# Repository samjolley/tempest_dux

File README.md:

# Tempest Dux

A wireless split ergonomic keyboard with an integrated trackball. Thirty-six keys, low-profile Choc switches, nice!nano v2, nice!view display, and a PMW3610 trackball on the right half.

This is my build. I did not design it from scratch, and the credits below matter.

## Lineage and credits

- **Ergonomics:** the dux family, Rae-Dux and Architeuthis Dux.
- **Base design and visual theme:** [thrly's Tempest](https://github.com/thrly/tempest).
- **Firmware base:** [Manna Harbour's Miryoku](https://github.com/manna-harbour/miryoku) for ZMK.
- **Trackball driver:** [badjeff's PMW3610 module](https://github.com/badjeff/zmk-pmw3610-driver).

## What is mine

Built on that lineage, my own contribution is:

- a custom PCB laid out with Ergogen and finished in KiCad (matrix, MCU, display, power, and the trackball cluster),
- the integrated PMW3610 trackball on the right half, its socket, and the printed housing,
- custom outlines and multi-layer 3D-printed plates and case,
- the ZMK firmware integration that makes the trackball a first-class input alongside the keys.

## Status

- **v0.6.56** boards fabricated and in assembly and bring-up.
- **v0.7.x** in progress: the reversible board architecture is dropped in favor of separate left and right files, with mounting-hole clearance, test points, and a dual-face ground pour on the errata list.

## Build log

I wrote up the design decisions, the failures, and what I would do differently here: <https://samjolley.com/writing/building-the-tempest-dux/>

## License

My original work here (the Ergogen config, the KiCad board, and my custom footprints) is released under the MIT License; see [LICENSE](LICENSE). Bundled third-party components keep their own licenses: the `ceoloide` Ergogen footprints under `ergogen/footprints/ceoloide/` retain the license headers in each file. This design builds on the prior art credited above, which carries its own terms where stated.

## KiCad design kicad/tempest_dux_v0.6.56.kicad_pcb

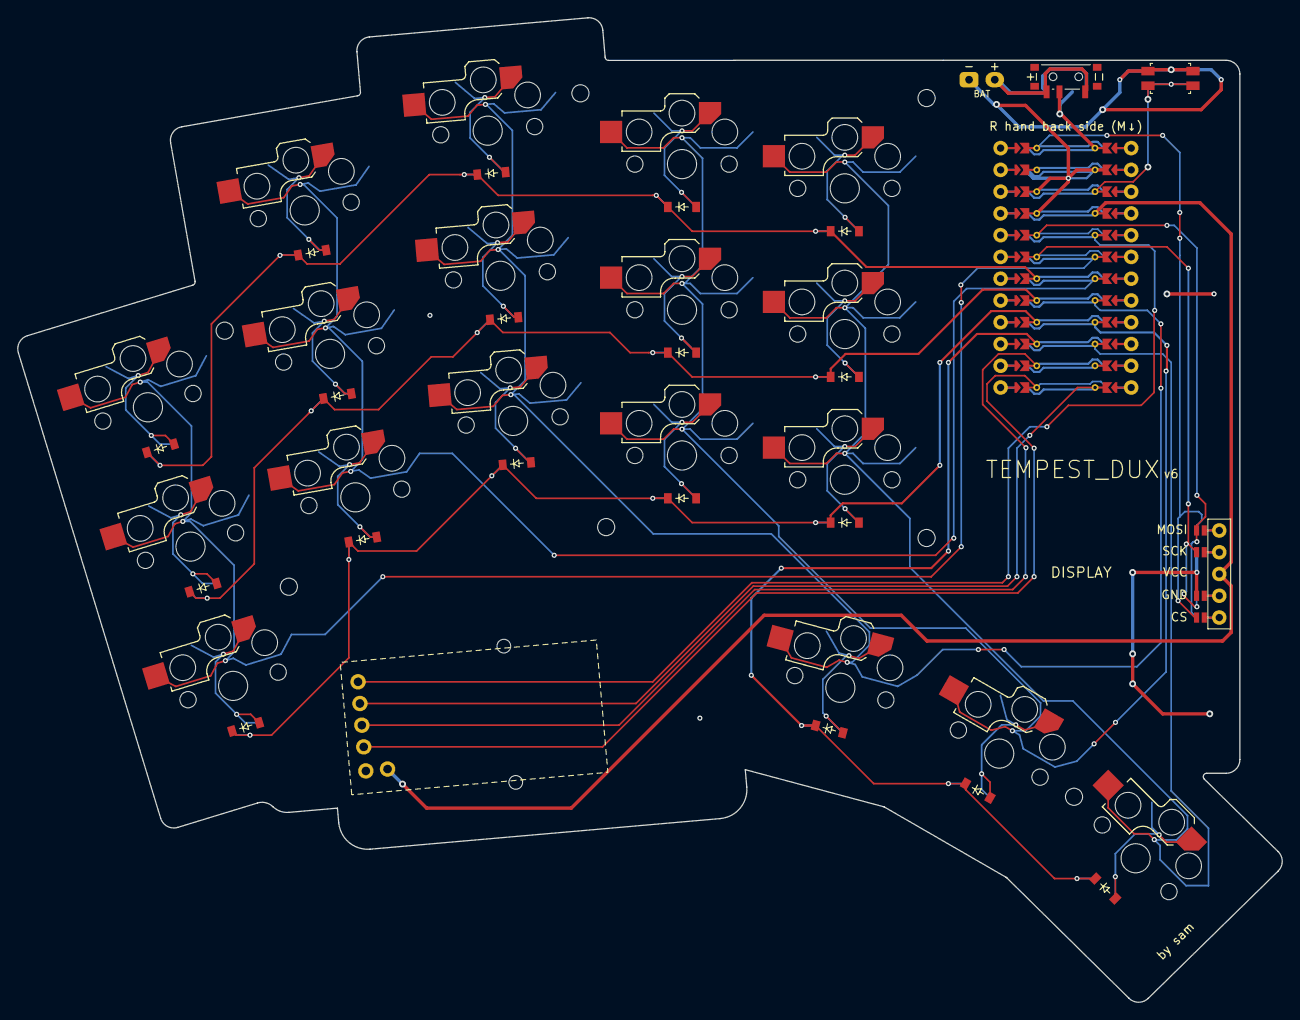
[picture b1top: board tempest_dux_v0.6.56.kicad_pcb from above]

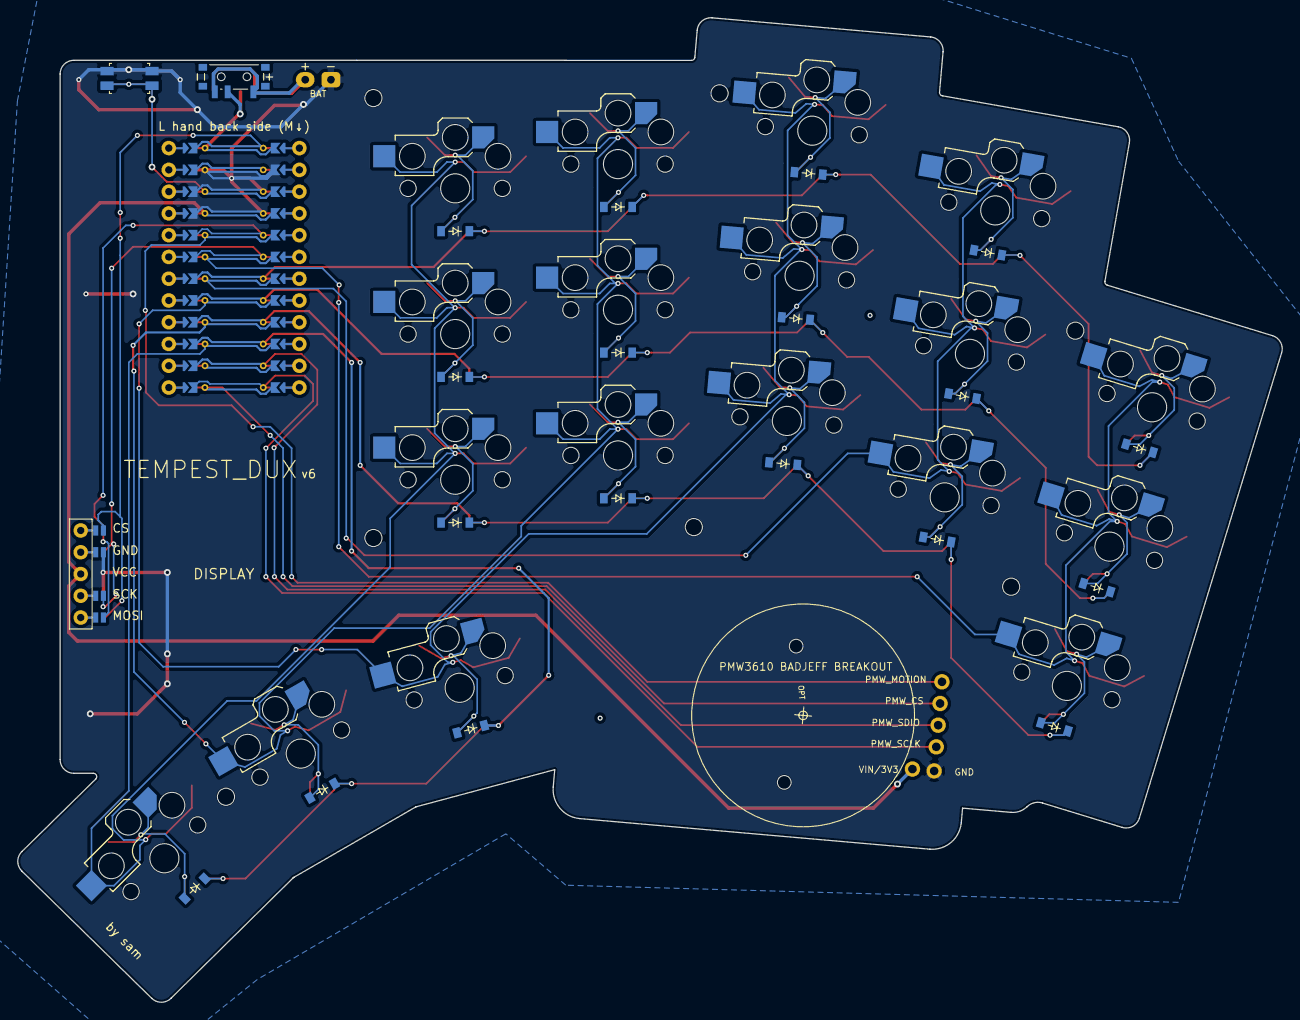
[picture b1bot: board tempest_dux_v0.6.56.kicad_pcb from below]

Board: 2 copper layers, 147.6 x 114.9 mm, 50 parts (18 on the bottom side), 43 nets.

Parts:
BAT1: battery_direct_solder_reversible
D1, D2, D3, D4, D5, D6, D7, D8, D9, D10, D11, D12, D13, D14, D15, D16, D17, D18: diode_tht_sod123
DISP1: display_nice_view
MCU1: mcu_nice_nano
MH1, MH2, MH3, MH4, MH5, MH6, MH7: mounting_hole_npth
PMW1: badjeff PMW3610 breakout socket; pmw3610_badjeff_socket
PWR1: power_switch_smd_side
RST1: reset_switch_smd_side
S1, S2, S3, S4, S5, S6, S7, S8, S9, S10, S11, S12, S13, S14, S15, S16, S17, S18: switch_choc_v1_v2
TB: keyball_34mm_case; keyball_trackball_case_34mm

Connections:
BAT_P: BAT1.2, PWR1.1, PWR1.3
CS: DISP1.14, DISP1.24, MCU1.124
DISP1_1: DISP1.1, DISP1.10, DISP1.23
DISP1_2: DISP1.2, DISP1.11, DISP1.22
DISP1_4: DISP1.4, DISP1.12, DISP1.21
DISP1_5: DISP1.5, DISP1.13, DISP1.20
GND: BAT1.1, DISP1.15, DISP1.25, MCU1.102, MCU1.121, MCU1.122, PMW1.GND, RST1.1, RST1.3
MOSI: DISP1.17, DISP1.27, MCU1.120
PMW_CS: MCU1.112, PMW1.CS
PMW_MOTION: MCU1.105, PMW1.MOTION
PMW_SCLK: MCU1.113, PMW1.SCLK
PMW_SDIO: MCU1.114, PMW1.SDIO
RAW: MCU1.101, PWR1.2
RST: MCU1.103, RST1.2, RST1.4
SCK: DISP1.16, DISP1.26, MCU1.119
VCC: DISP1.3, MCU1.104, PMW1.VIN
col_index: MCU1.109, S10.2, S11.2, S12.2, S17.2
col_inner: MCU1.110, S13.2, S14.2, S15.2, S18.2
col_middle: MCU1.108, S7.2, S8.2, S9.2, S16.2
col_pinky: MCU1.106, S1.2, S2.2, S3.2
col_ring: MCU1.107, S4.2, S5.2, S6.2
far_thumb-cluster: D18.2, S18.1
index_bottom: D10.2, S10.1
index_home: D11.2, S11.1
index_top: D12.2, S12.1
inner_bottom: D13.2, S13.1
inner_home: D14.2, S14.1
inner_top: D15.2, S15.1
mid_thumb-cluster: D17.2, S17.1
middle_bottom: D7.2, S7.1
middle_home: D8.2, S8.1
middle_top: D9.2, S9.1
near_thumb-cluster: D16.2, S16.1
pinky_bottom: D1.2, S1.1
pinky_home: D2.2, S2.1
pinky_top: D3.2, S3.1
ring_bottom: D4.2, S4.1
ring_home: D5.2, S5.1
ring_top: D6.2, S6.1
row_bottom: D1.1, D4.1, D7.1, D10.1, D13.1, MCU1.116
row_home: D2.1, D5.1, D8.1, D11.1, D14.1, MCU1.117
row_thumb: D16.1, D17.1, D18.1, MCU1.115
row_top: D3.1, D6.1, D9.1, D12.1, D15.1, MCU1.118

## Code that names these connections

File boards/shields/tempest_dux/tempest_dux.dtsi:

/*
 * Tempest Dux shared configuration (both halves).
 *
 * All pins verified against the v0.6.56 KiCad netlist (MCU1 pads 101-124):
 *   rows:  pro_micro 4/5/6/7   = row_top / row_home / row_bottom / row_thumb
 *   cols:  pro_micro 20/19/18/15/14 = col_pinky / ring / middle / index / inner
 *   PMW3610: SCLK P1.06 (pm9), SDIO P1.04 (pm8, 3-wire), nCS P0.09 (pm10),
 *            MOTION P0.31 (pm21, R1 pull-up DNP -> internal pull-up)
 *   display: stock nice_view_adapter pins (CS P0.06, MOSI P0.17, SCK P0.20)
 *
 * The ceoloide reversible MCU footprint cross-connects on B.Cu, so the same
 * pro_micro numbers carry the matrix and trackball on both halves.
 */

#include <dt-bindings/zmk/matrix_transform.h>
#include <dt-bindings/pinctrl/nrf-pinctrl.h>
#include <zephyr/dt-bindings/input/input-event-codes.h>

/ {
    chosen {
        zmk,physical-layout = &default_layout;
    };

    default_layout: physical_layout0 {
        compatible = "zmk,physical-layout";
        display-name = "Default";
        transform = <&default_transform>;
        kscan = <&kscan0>;
    };

    default_transform: keymap_transform0 {
        compatible = "zmk,matrix-transform";
        columns = <10>;
        rows = <4>;
        // Emits minidox.h order: 3x10 alphas, then thumbs L near->far, R far->near.
        // Right half is the mirrored reversible board, so its row entries run 9->5.
        // VERIFY on hardware: if a left thumb fires the wrong miryoku thumb,
        // reverse the three RC(3,x) left entries and mirror the right.
        map = <
RC(0,0) RC(0,1) RC(0,2) RC(0,3) RC(0,4)    RC(0,9) RC(0,8) RC(0,7) RC(0,6) RC(0,5)
RC(1,0) RC(1,1) RC(1,2) RC(1,3) RC(1,4)    RC(1,9) RC(1,8) RC(1,7) RC(1,6) RC(1,5)
RC(2,0) RC(2,1) RC(2,2) RC(2,3) RC(2,4)    RC(2,9) RC(2,8) RC(2,7) RC(2,6) RC(2,5)
                RC(3,2) RC(3,3) RC(3,4)    RC(3,9) RC(3,8) RC(3,7)
        >;
    };

    kscan0: kscan0 {
        compatible = "zmk,kscan-gpio-matrix";
        diode-direction = "col2row";
        wakeup-source;

        // col2row: rows are sensed inputs, cols are strobed outputs
        row-gpios
            = <&pro_micro 4 (GPIO_ACTIVE_HIGH | GPIO_PULL_DOWN)>   // row_top
            , <&pro_micro 5 (GPIO_ACTIVE_HIGH | GPIO_PULL_DOWN)>   // row_home
            , <&pro_micro 6 (GPIO_ACTIVE_HIGH | GPIO_PULL_DOWN)>   // row_bottom
            , <&pro_micro 7 (GPIO_ACTIVE_HIGH | GPIO_PULL_DOWN)>   // row_thumb
            ;

        col-gpios
            = <&pro_micro 20 GPIO_ACTIVE_HIGH>   // col_pinky   (col 0)
            , <&pro_micro 19 GPIO_ACTIVE_HIGH>   // col_ring    (col 1)
            , <&pro_micro 18 GPIO_ACTIVE_HIGH>   // col_middle  (col 2)
            , <&pro_micro 15 GPIO_ACTIVE_HIGH>   // col_index   (col 3)
            , <&pro_micro 14 GPIO_ACTIVE_HIGH>   // col_inner   (col 4)
            ;
    };

    // Local trackball -> pointer events. Enabled per-half in the overlays.
    trackball_listener: trackball_listener {
        compatible = "zmk,input-listener";
        status = "disabled";
        device = <&trackball>;
    };

    // Forwarding channel for the peripheral half's trackball.
    split_inputs {
        #address-cells = <1>;
        #size-cells = <0>;

        trackball_split: trackball_split@0 {
            compatible = "zmk,input-split";
            reg = <0>;
        };
    };

    // Central-side listener for events arriving over the split link.
    trackball_split_listener: trackball_split_listener {
        compatible = "zmk,input-listener";
        status = "disabled";
        device = <&trackball_split>;
    };
};

// PMW3610 on its own SPI bus (spi1) so it never collides with the
// display on spi0/pro_micro_spi (left half).
&pinctrl {
    spi1_trackball_default: spi1_trackball_default {
        group1 {
            psels = <NRF_PSEL(SPIM_SCK,  1, 6)>,   // PMW_SCLK  P1.06 / pm9
                    <NRF_PSEL(SPIM_MOSI, 1, 4)>,   // PMW_SDIO  P1.04 / pm8
                    <NRF_PSEL(SPIM_MISO, 1, 4)>;   // same pin: 3-wire SDIO
        };
    };

    spi1_trackball_sleep: spi1_trackball_sleep {
        group1 {
            psels = <NRF_PSEL(SPIM_SCK,  1, 6)>,
                    <NRF_PSEL(SPIM_MOSI, 1, 4)>,
                    <NRF_PSEL(SPIM_MISO, 1, 4)>;
            low-power-enable;
        };
    };
};

&spi1 {
    status = "okay";
    compatible = "nordic,nrf-spim";
    pinctrl-0 = <&spi1_trackball_default>;
    pinctrl-1 = <&spi1_trackball_sleep>;
    pinctrl-names = "default", "sleep";
    cs-gpios = <&pro_micro 10 GPIO_ACTIVE_LOW>;   // PMW_CS / P0.09

    trackball: trackball@0 {
        status = "okay";
        compatible = "pixart,pmw3610-alt";
        reg = <0>;
        spi-max-frequency = <2000000>;
        // MOTION is active-low; on-board R1 pull-up is DNP -> internal pull-up
        irq-gpios = <&pro_micro 21 (GPIO_ACTIVE_LOW | GPIO_PULL_UP)>;
        cpi = <600>;
        evt-type = <INPUT_EV_REL>;
        x-input-code = <INPUT_REL_X>;
        y-input-code = <INPUT_REL_Y>;
        // VERIFY orientation on first roll; flip as needed:
        // swap-xy; invert-x; invert-y;
    };
};

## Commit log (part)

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2026-05-13 Rename project to TEMPEST_DUX and modify description
    Updated project name and description in README.md.
2026-05-22 feat(zmk): init config structure with miryoku and pointer support
2026-05-22 feat(zmk): add dtsi/overlay with input-split and pmw3610 pin mapping
2026-06-10 fix(zmk): netlist-verified pins, badjeff driver wiring, and buildable config
    The initial config on feat/zmk-base could not work against the v0.6.56
    PCBs:
    - the kscan rows/cols it referenced were actually column nets plus the
    PMW3610 MOTION line (and one unrouted pin), per the KiCad netlist
    - the trackball used compatible "pixart,pmw3610" which matches no driver
    in badjeff/zmk-pmw3610-driver (binding is pixart,pmw3610-alt) and was
2026-06-10 fix(ci): use post-Zephyr-4.1 board target nice_nano@2.0.0//zmk
    ZMK main renamed nice_nano_v2 as part of the Zephyr 4.1 / hardware
    model v2 migration (zmk.dev blog 2025-12-09); the old name no longer
    resolves and all three builds failed with 'Invalid BOARD'.
    https://claude.ai/code/session_0175L4aN9pPvUSa2cpTh2Vb6
2026-06-10 fix(build): move miryoku under config/ so the isolated CI build can find it
    The build-user-config workflow copies only config/ to an isolated
    directory, so the keymap's ../miryoku includes resolved to nothing.
    https://claude.ai/code/session_0175L4aN9pPvUSa2cpTh2Vb6
